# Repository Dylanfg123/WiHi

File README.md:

View this project on [CADLAB.io](https://cadlab.io/project/26850). 

# WiHi

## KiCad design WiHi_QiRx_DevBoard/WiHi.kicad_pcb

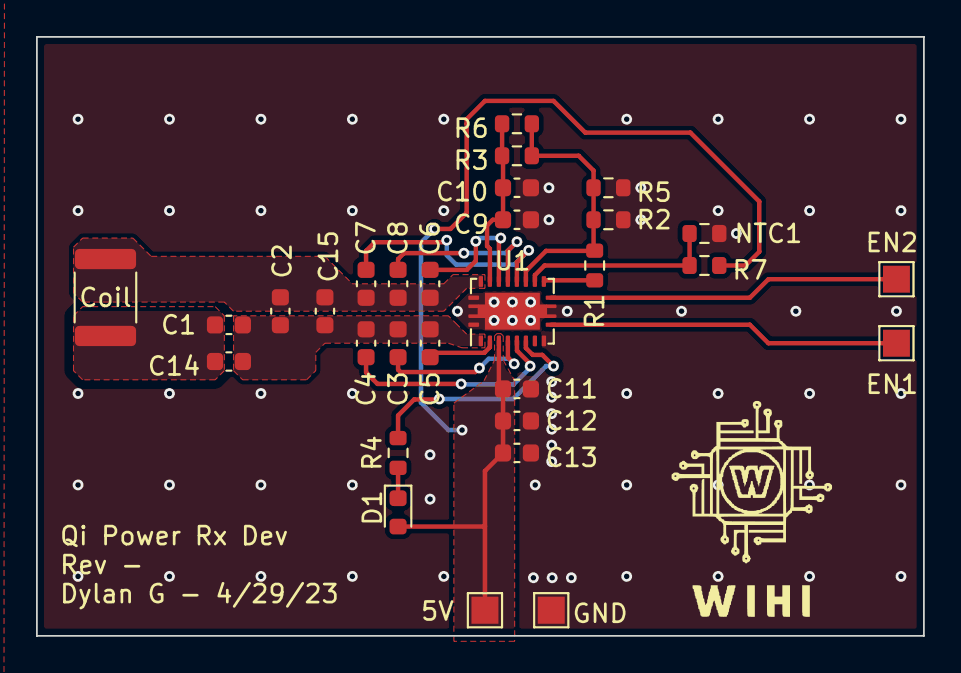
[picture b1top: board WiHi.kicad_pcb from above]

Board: 2 copper layers, 49.3 x 33.3 mm, 30 parts (0 on the bottom side), 19 nets.

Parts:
5V: TestPoint_Pad_1.5x1.5mm
C1: 0.12u; C_0603_1608Metric
C2: 2n; C_0603_1608Metric
C3, C8: 4.7u; C_0603_1608Metric
C4, C7: 22n; C_0603_1608Metric
C5, C6, C14: 10n; C_0603_1608Metric
C9, C11, C12: 10u; C_0603_1608Metric
C10, C13: 0.1u; C_0603_1608Metric
C15: C; C_0603_1608Metric
Coil: 13.3u; L_1812_4532Metric
D1: LED; LED_0603_1608Metric
EN1, EN2: TestPoint_Pad_1.5x1.5mm
GND: TestPoint_Pad_1.5x1.5mm
NTC1: Thermistor_NTC_US; R_0603_1608Metric
R1: 66; R_0603_1608Metric
R2: 196; R_0603_1608Metric
R3: 20k; R_0603_1608Metric
R4, R7: 1k5; R_0603_1608Metric
R5, R6: R_0603_1608Metric
U1: BQ51013BRHLR; Texas_VQFN-RHL-20

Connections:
/Wireless Power Reciever Qi/AC1: C1.2, C2.2, C3.1, C4.1, C5.1, C14.2, C15.2, U1.2 (AC1)
/Wireless Power Reciever Qi/AC2: C2.1, C6.1, C7.1, C8.1, C15.1, Coil.2, U1.19 (AC2)
/Wireless Power Reciever Qi/BOOT1: C5.2, U1.3 (BOOT1)
/Wireless Power Reciever Qi/BOOT2: C6.2, U1.17 (BOOT2)
/Wireless Power Reciever Qi/CHG: R4.2, U1.7 (~CHG)
/Wireless Power Reciever Qi/CLAMP1: C3.2, U1.5 (CLAMP1)
/Wireless Power Reciever Qi/CLAMP2: C8.2, U1.16 (CLAMP2)
/Wireless Power Reciever Qi/COMM1: C4.2, U1.6 (COMM1)
/Wireless Power Reciever Qi/COMM2: C7.2, U1.15 (COMM2)
/Wireless Power Reciever Qi/EN1: EN1.1, U1.10 (EN1)
/Wireless Power Reciever Qi/EN2: EN2.1, U1.11 (EN2)
/Wireless Power Reciever Qi/FOD: R1.2, R2.2, R3.2, R5.2, R6.1, U1.14 (FOD)
/Wireless Power Reciever Qi/ILIM: R1.1, U1.12 (ILIM)
/Wireless Power Reciever Qi/Qi_Vout: 5V.1, C11.2, C12.2, C13.2, D1.2 (A), R7.1, U1.4 (OUT)
/Wireless Power Reciever Qi/RECT: C9.2, C10.2, R3.1, R6.2, U1.18 (RECT)
/Wireless Power Reciever Qi/RX1: C1.1, C14.1, Coil.1
/Wireless Power Reciever Qi/TSCTRL: NTC1.1, R7.2, U1.13 (TS/CTRL)
GND: C9.1, C10.1, C11.1, C12.1, C13.1, GND.1, NTC1.2, R2.1, R5.1, U1.1 (PGND), U1.9 (AD), U1.20 (PGND), U1.21 (PGND)
unnamed: D1.1 (K), R4.1

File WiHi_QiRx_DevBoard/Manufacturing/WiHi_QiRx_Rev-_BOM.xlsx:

null | References | Value | Footprint | Digikey | Quantity
1 | C5, C6, C14 | 10n | C_0603_1608Metric | 478-5007-1-ND | 3
2 | C9, C11, C12 | 10u | C_0603_1608Metric | 490-13248-1-ND | 3
3 | C3, C8 | 4.7u | C_0603_1608Metric | 445-9064-1-ND | 2
4 | C4, C7 | 22n | C_0603_1608Metric | 445-5663-1-ND | 2
5 | C10, C13 | 0.1u | C_0603_1608Metric | 1276-1935-1-ND | 2
6 | C1 | 0.12u | C_0603_1608Metric | 399-9962-1-ND | 1
7 | C2 | 2n | C_0603_1608Metric | 490-GCM1885C1H202FA16DCT-ND | 1
8 | C15 | C | C_0603_1608Metric |  | 1
9 | R4, R7 | 1k5 | R_0603_1608Metric | RHM1.50KADCT-ND | 2
10 | R5, R6 | ~ | R_0603_1608Metric |  | 2
11 | R1 | 66 | R_0603_1608Metric | 311-66.5HRCT-ND | 1
12 | R2 | 196 | R_0603_1608Metric | 311-196HRCT-ND | 1
13 | R3 | 20k | R_0603_1608Metric | 311-20.0KHRCT-ND | 1
14 | D1 | LED | LED_0603_1608Metric | 160-1183-1-ND | 1
15 | U1 | BQ51013BRHLR | Texas_VQFN-RHL-20 | 296-38885-1-ND | 1
16 | 5V, EN1, EN2, GND | ~ | TestPoint_Pad_1.5x1.5mm |  | 4
17 | Coil | 13.3u | L_1812_4532Metric | 445-16090-ND | 1
18 | NTC1 | Thermistor_NTC_US | R_0603_1608Metric | 490-16279-1-ND | 1

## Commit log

2023-04-30 Initial commit - adding all project files
2023-04-30 Backlink to CADLAB.io has been added.
2023-04-30 Added README file
2023-05-13 adding gitignore
